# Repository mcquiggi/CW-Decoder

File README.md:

# Easy CW Decoder
Arduino Sketch, interface schematic and PCB for decoding CW as per my articles in _The Communicator_, summer 2024.

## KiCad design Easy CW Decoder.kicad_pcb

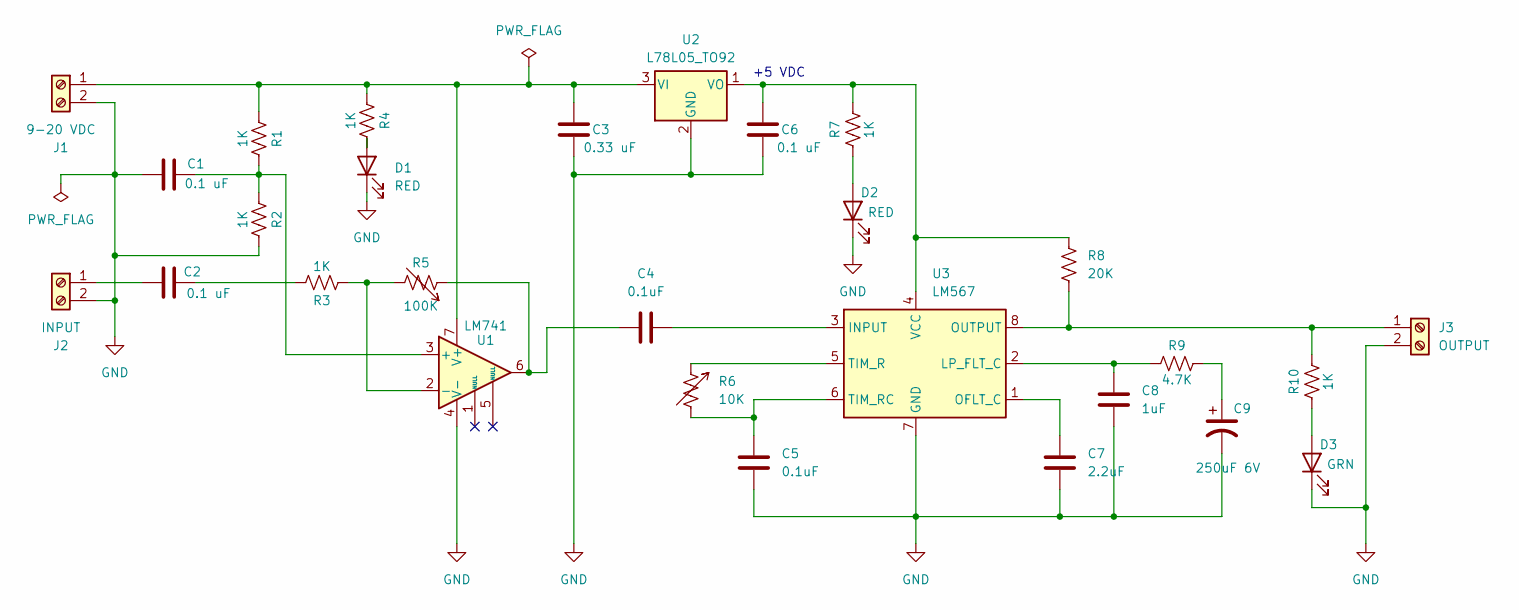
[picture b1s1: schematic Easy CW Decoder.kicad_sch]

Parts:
C1, C2, C6: 0.1 uF; C_Rect_L4.0mm_W2.5mm_P2.50mm
C3: 0.33 uF; C_Rect_L4.0mm_W2.5mm_P2.50mm
C4, C5: 0.1uF; C_Rect_L4.0mm_W2.5mm_P2.50mm
C7: 2.2uF; C_Rect_L4.0mm_W2.5mm_P2.50mm
C8: 1uF; C_Rect_L4.0mm_W2.5mm_P2.50mm
C9: 250uF 6V; CP_Radial_D8.0mm_P3.50mm
D1, D2: RED; LED_D5.0mm
D3: GRN; LED_D5.0mm
J1: 9-20 VDC; Altech_AK100_1x02_P5.00mm
J2: INPUT; Altech_AK100_1x02_P5.00mm
J3: OUTPUT; Altech_AK100_1x02_P5.00mm
R1, R2, R3, R4, R7, R10: 1K; R_Axial_DIN0204_L3.6mm_D1.6mm_P7.62mm_Horizontal
R5: 100K; Altech_AK100_1x02_P5.00mm
R6: 10K; Altech_AK100_1x02_P5.00mm
R8: 20K; R_Axial_DIN0204_L3.6mm_D1.6mm_P7.62mm_Horizontal
R9: 4.7K; R_Axial_DIN0204_L3.6mm_D1.6mm_P7.62mm_Horizontal
U1: LM741; DIP-8_W7.62mm_Socket
U2: L78L05_TO92; TO-92_Inline
U3: LM567; DIP-8_W7.62mm_Socket

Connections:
GND: C1.1, C3.2, C5.2, C6.2, C7.2, C8.2, C9.2, D1.1 (K), D2.1 (K), D3.1 (K), J1.2, J2.2, J3.2, R2.1, U1.4 (V-), U2.2 (GND), U3.7 (GND)
unnamed: C2.1, R3.1
unnamed: C4.2, R5.1, U1.6
unnamed: C9.1, R9.1
unnamed: D1.2 (A), R4.1
unnamed: D2.2 (A), R7.2
unnamed: D3.2 (A), R10.2
unnamed: C3.1, J1.1, R1.2, R4.2, U1.7 (V+), U2.3 (VI)
unnamed: C2.2, J2.1
unnamed: J3.1, R8.2, R10.1, U3.8 (OUTPUT)
unnamed: C1.2, R1.1, R2.2, U1.3 (+)
unnamed: R3.2, R5.2, U1.2 (-)
unnamed: C6.1, R7.1, R8.1, U2.1 (VO), U3.4 (VCC)
unnamed: C4.1, U3.3 (INPUT)
unnamed: C8.1, R9.2, U3.2 (LP_FLT_C)
unnamed: C7.1, U3.1 (OFLT_C)
unnamed: R6.1, U3.5 (TIM_R)
unnamed: C5.1, R6.2, U3.6 (TIM_RC)

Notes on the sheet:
+5 VDC

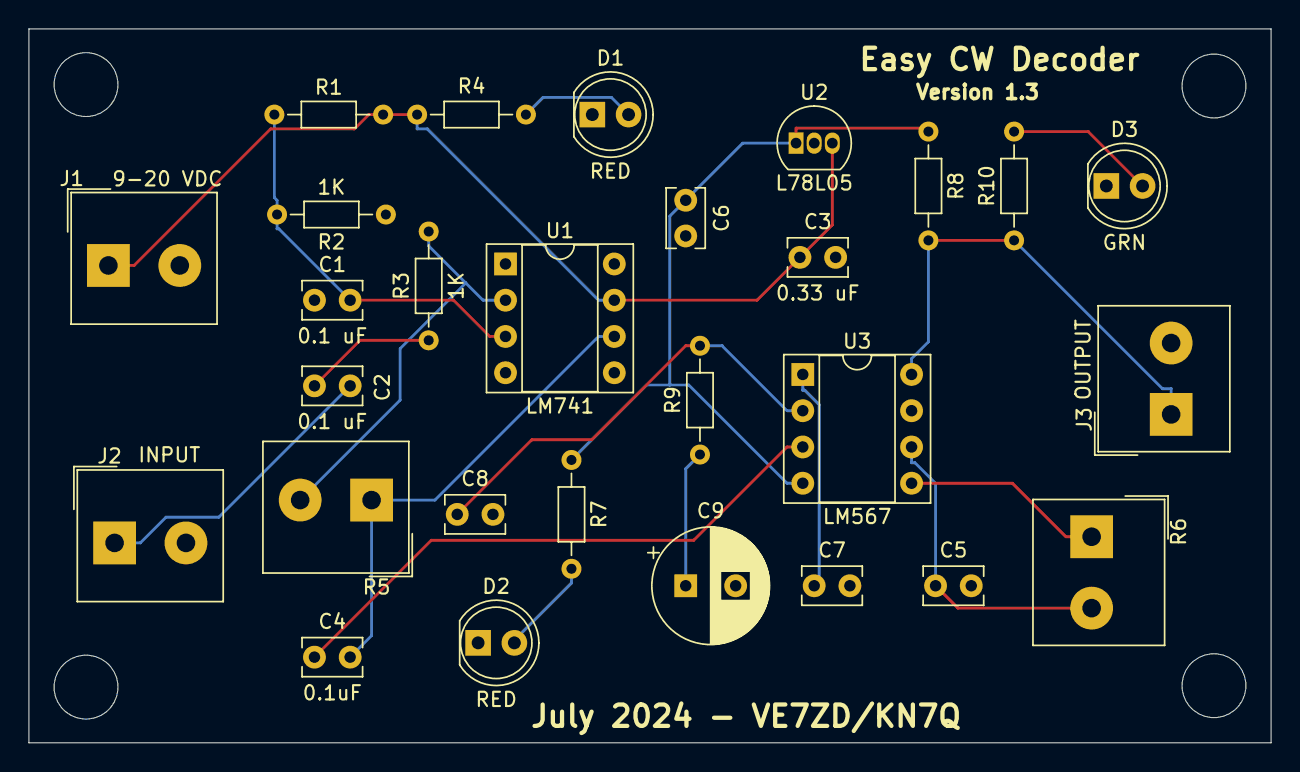
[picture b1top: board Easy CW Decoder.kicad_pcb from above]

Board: 2 copper layers, 87.0 x 50.0 mm, 28 parts (0 on the bottom side), 18 nets.

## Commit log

2024-06-27 Added GPL notice to Sketch and added LICENCE.TXT
2024-08-19 Add files via upload
    Added hardware interface schematic and draft PCB files
2024-08-27 Add files via upload
    Updated the schematic and PCB files to the latest version as referenced in The Communicator, Sept/Oct 2024.
2024-08-27 Add files via upload
    Updated schematic and PCB files to reflect the article in The Communicator, September 2024.
